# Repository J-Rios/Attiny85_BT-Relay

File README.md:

# Attiny85_BT-Relay
Attiny85 based custom board to control a relay via bluetooth (with Arduino code).
[See Image.](Image.png)

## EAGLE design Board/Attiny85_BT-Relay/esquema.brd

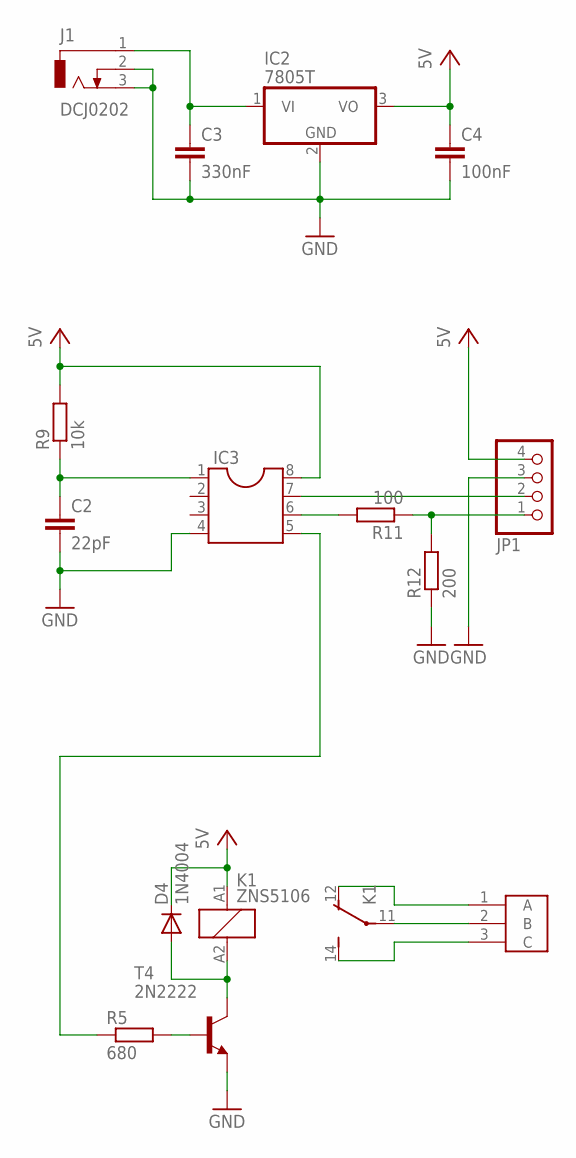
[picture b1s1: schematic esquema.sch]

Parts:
C2: 22pF; C050-025X075
C3: 330nF; C050-025X075
C4: 100nF; C050-025X075
D4: 1N4004; DO41-10
IC2: 7805T; TO220H
IC3: DIL8S; SOCKET-08
J1: DCJ0202
JP1: PINHD-1X4; 1X04
K1: ZNS5106; ZN5
R5: 680; 0204/7
R9: 10k; 0204/7
R11: 100; 0204/7
R12: 200; 0204/7
T4: 2N2222; TO18
U$1: POT_CONNECTOR

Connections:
GND: C2.2, C3.2, C4.2, IC2.2 (GND), IC3.4, J1.2, J1.3, JP1.3, R12.1, T4.1 (E)
unnamed: IC3.7, JP1.2
unnamed: K1.11, U$1.2 (B)
unnamed: IC3.6, R11.2
unnamed: K1.12 (O), U$1.1 (A)
unnamed: K1.14 (S), U$1.3 (C)
unnamed: D4.A, K1.A2 (2), T4.3 (C)
unnamed: R5.2, T4.2 (B)
unnamed: C2.1, IC3.1, R9.1
unnamed: C3.1, IC2.1 (VI), J1.1
unnamed: JP1.1, R11.1, R12.2
unnamed: IC3.5, R5.1
VCC: C4.1, D4.C, IC2.3 (VO), IC3.8, JP1.4, K1.A1 (1), R9.2

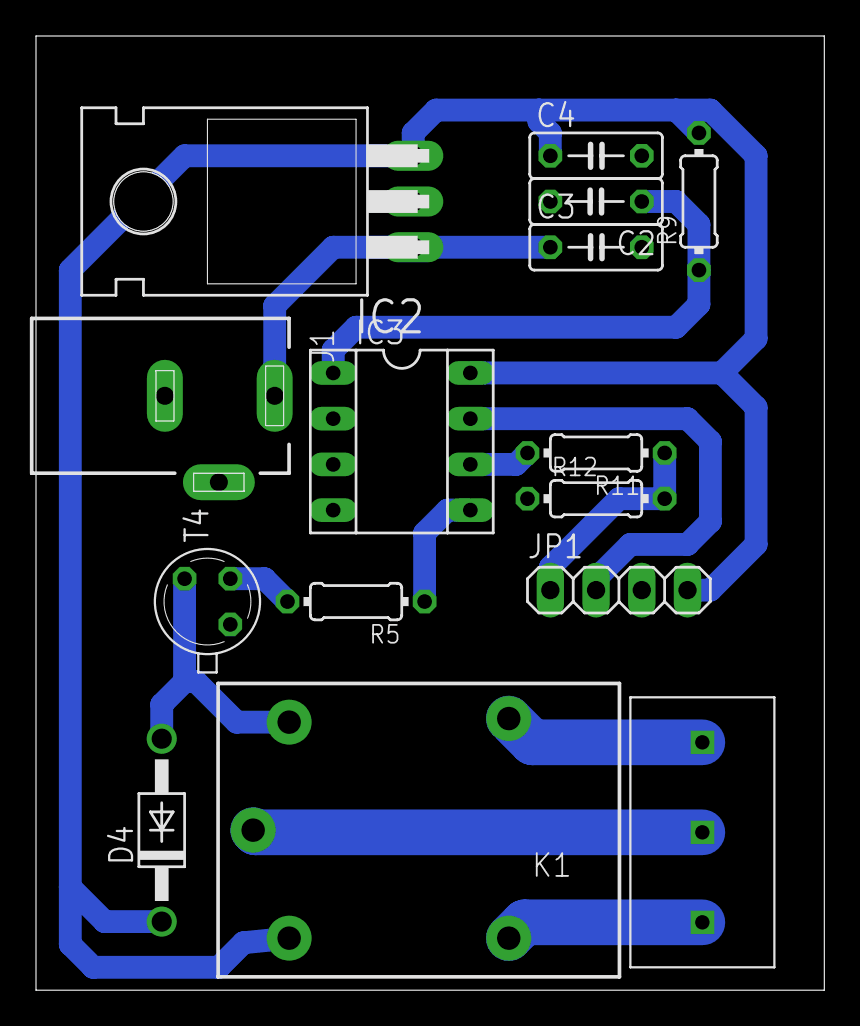
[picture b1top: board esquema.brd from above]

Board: 2 copper layers, 43.8 x 53.0 mm, 15 parts (0 on the bottom side), 13 nets.

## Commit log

2015-04-27 Code
    Arduino code
2015-04-27 Board
    Eagle board
2015-04-27 Code
2015-05-10 Image
    Image added
2015-05-14 Delete files
    Delete dummy files of the Eagle board project
